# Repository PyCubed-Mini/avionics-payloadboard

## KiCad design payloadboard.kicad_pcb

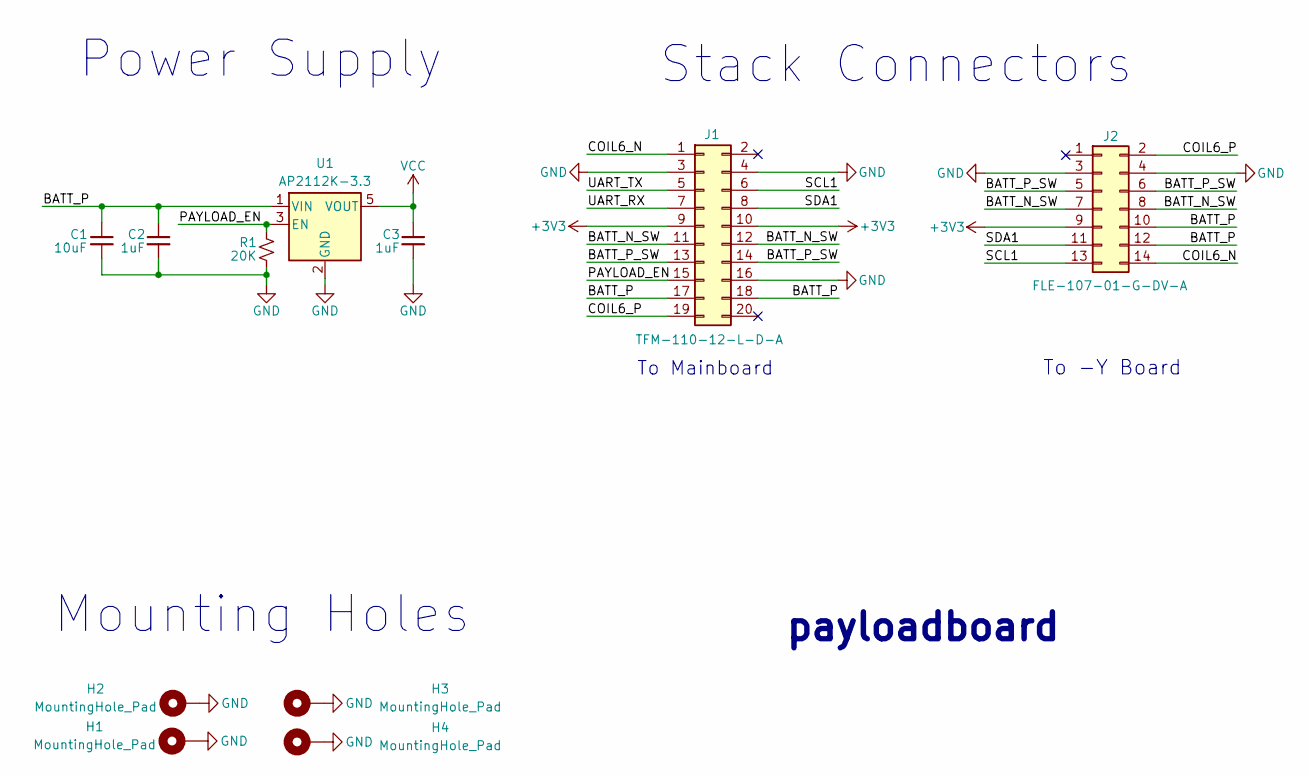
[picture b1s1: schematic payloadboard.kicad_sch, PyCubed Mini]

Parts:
C1: 10uF; C_0805_2012Metric
C2, C3: 1uF; C_0805_2012Metric
H1, H2, H3, H4: MountingHole_Pad; MountingHole
J1: TFM-110-12-L-D-A; SAMTEC_TFM-110-12-L-D-A
J2: FLE-107-01-G-DV-A; SAMTEC_FLE-107-01-G-DV-A
R1: 20K; R_0805_2012Metric
U1: AP2112K-3.3; SOT-23-5

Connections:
+3V3: J1.9, J1.10, J2.9
/BATT_N_SW: J1.11, J1.12, J2.7, J2.8
/BATT_P: C1.1, C2.1, J1.17, J1.18, J2.10, J2.12, U1.1 (VIN)
/BATT_P_SW: J1.13, J1.14, J2.5, J2.6
/COIL6_N: J1.1, J2.14
/COIL6_P: J1.19, J2.2
/PAYLOAD_EN: J1.15, R1.1, U1.3 (EN)
/SCL1: J1.6, J2.13
/SDA1: J1.8, J2.11
/UART_RX: J1.7
/UART_TX: J1.5
GND: C1.2, C2.2, C3.2, H1.1, H2.1, H3.1, H4.1, J1.3, J1.4, J1.16, J2.3, J2.4, R1.2, U1.2 (GND)
VCC: C3.1, U1.5 (VOUT)

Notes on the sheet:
To Mainboard
Power Supply
Stack Connectors
To -Y Board
payloadboard
Mounting Holes

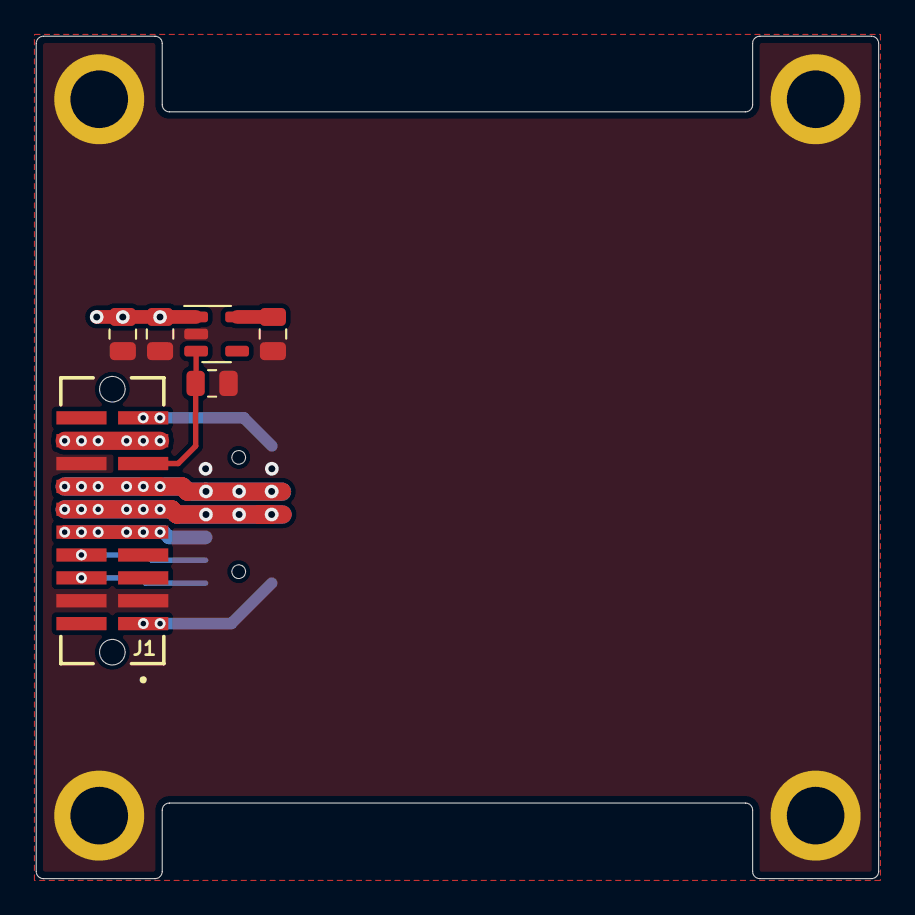
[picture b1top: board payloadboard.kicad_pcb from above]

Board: 2 copper layers, 46.8 x 46.8 mm, 12 parts (1 on the bottom side), 11 nets.

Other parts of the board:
Ref**: Val**; pycubed_mini_half

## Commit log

2022-09-08 B1/02 Updates
2022-09-08 Initialize kicad_libs
2022-09-09 Rerouted traces for better GND connection
2022-09-13 Exported Files
2022-10-09 Added 3.3V power regulator with enable pin and new stack connector
2022-11-09 Minor updates and export STEP / BOM
2022-11-11 Export Gerbers
